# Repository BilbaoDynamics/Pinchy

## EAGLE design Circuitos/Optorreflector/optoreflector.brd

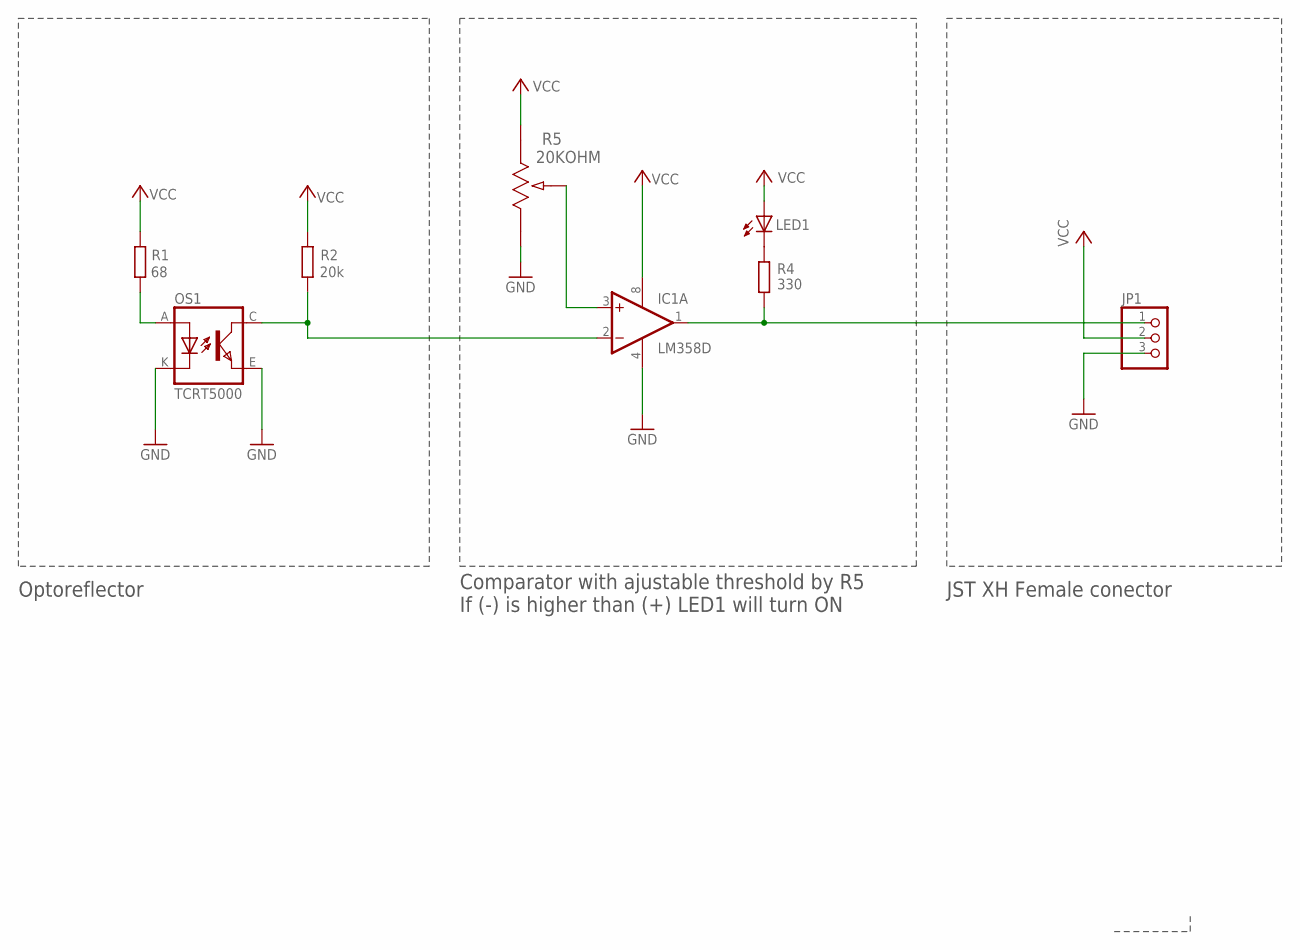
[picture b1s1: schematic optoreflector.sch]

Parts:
IC1: LM358D; SO08
JP1: PINHD-1X3; 1X03
LED1: LEDCHIP-LED0805; CHIP-LED0805
OS1: TCRT5000
R1: 68; R0805
R2: 20k; R0805
R4: 330; R0805
R5: 20KOHM; POT_EVM2W

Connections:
GND: IC1.4 (V-), JP1.3, OS1.E (EMITTER), OS1.K (CATHODE), R5.3
unnamed: LED1.C, R4.2
unnamed: OS1.A (ANODE), R1.1
unnamed: IC1.2 (-IN), OS1.C (COLLECTOR), R2.1
unnamed: IC1.3 (+IN), R5.2
unnamed: IC1.1 (OUT), JP1.1, R4.1
VCC: IC1.8 (V+), JP1.2, LED1.A, R1.2, R2.2, R5.1

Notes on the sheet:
Optoreflector
JST XH Female conector
Comparator with ajustable threshold by R5 If (-) is higher than (+) LED1 will turn ON

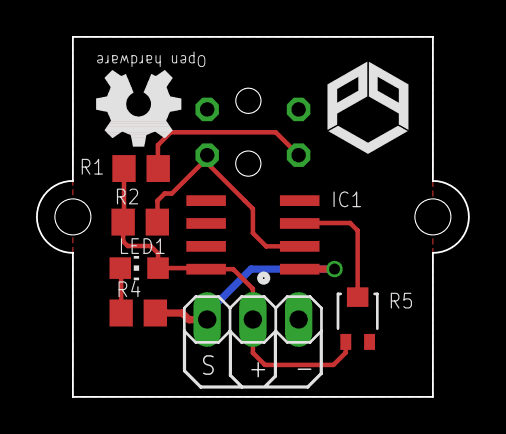
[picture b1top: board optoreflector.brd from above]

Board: 2 copper layers, 24.0 x 20.0 mm, 8 parts (1 on the bottom side), 7 nets.

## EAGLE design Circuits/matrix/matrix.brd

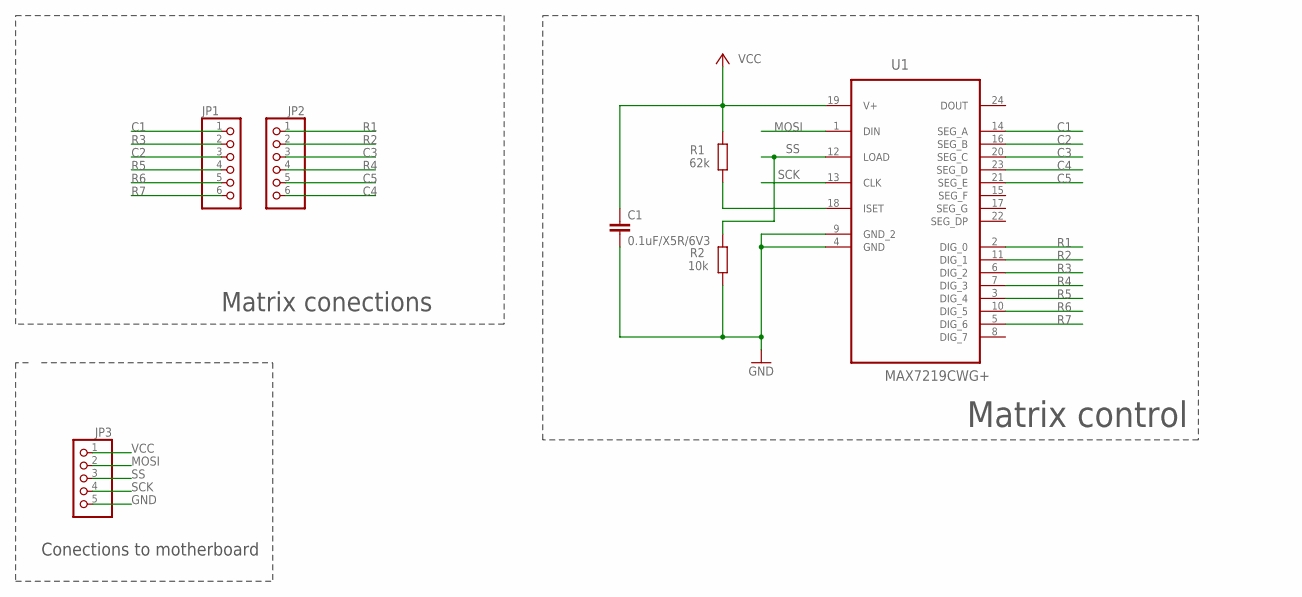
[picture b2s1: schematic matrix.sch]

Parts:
C1: 0.1uF/X5R/6V3; C1206
JP1, JP2: PINHD-1X6; 1X06
JP3: PINHD-1X5; 1X05
R1: 62k; R0805
R2: 10k; R0805
U1: MAX7219CWG+; SOIC127P1032X265-24N

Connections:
C1: JP1.1, U1.14 (SEG_A)
C2: JP1.3, U1.16 (SEG_B)
C3: JP2.3, U1.20 (SEG_C)
C4: JP2.6, U1.23 (SEG_D)
C5: JP2.5, U1.21 (SEG_E)
GND: C1.2, JP3.5, R2.1, U1.4 (GND), U1.9 (GND_2)
MOSI: JP3.2, U1.1 (DIN)
unnamed: R1.1, U1.18 (ISET)
R1: JP2.1, U1.2 (DIG_0)
R2: JP2.2, U1.11 (DIG_1)
R3: JP1.2, U1.6 (DIG_2)
R4: JP2.4, U1.7 (DIG_3)
R5: JP1.4, U1.3 (DIG_4)
R6: JP1.5, U1.10 (DIG_5)
R7: JP1.6, U1.5 (DIG_6)
SCK: JP3.4, U1.13 (CLK)
SS: JP3.3, R2.2, U1.12 (LOAD)
VCC: C1.1, JP3.1, R1.2, U1.19 (V+)

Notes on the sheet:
Matrix conections
Conections to motherboard
Matrix control

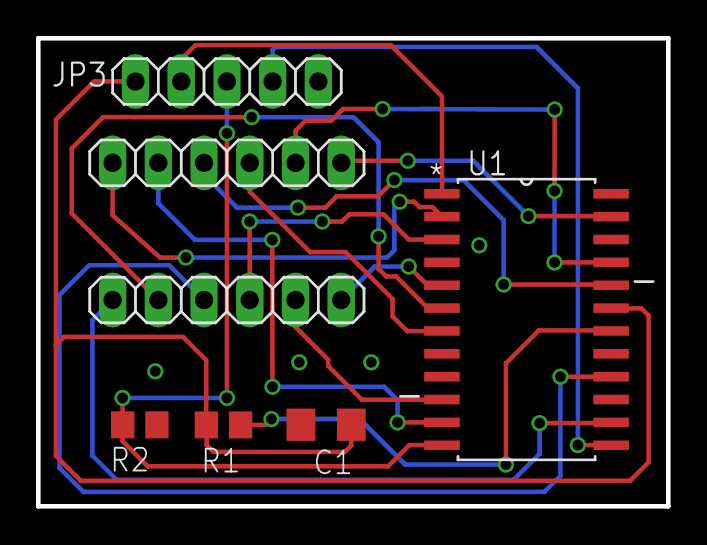
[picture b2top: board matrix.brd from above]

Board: 2 copper layers, 35.0 x 26.0 mm, 7 parts (0 on the bottom side), 18 nets.

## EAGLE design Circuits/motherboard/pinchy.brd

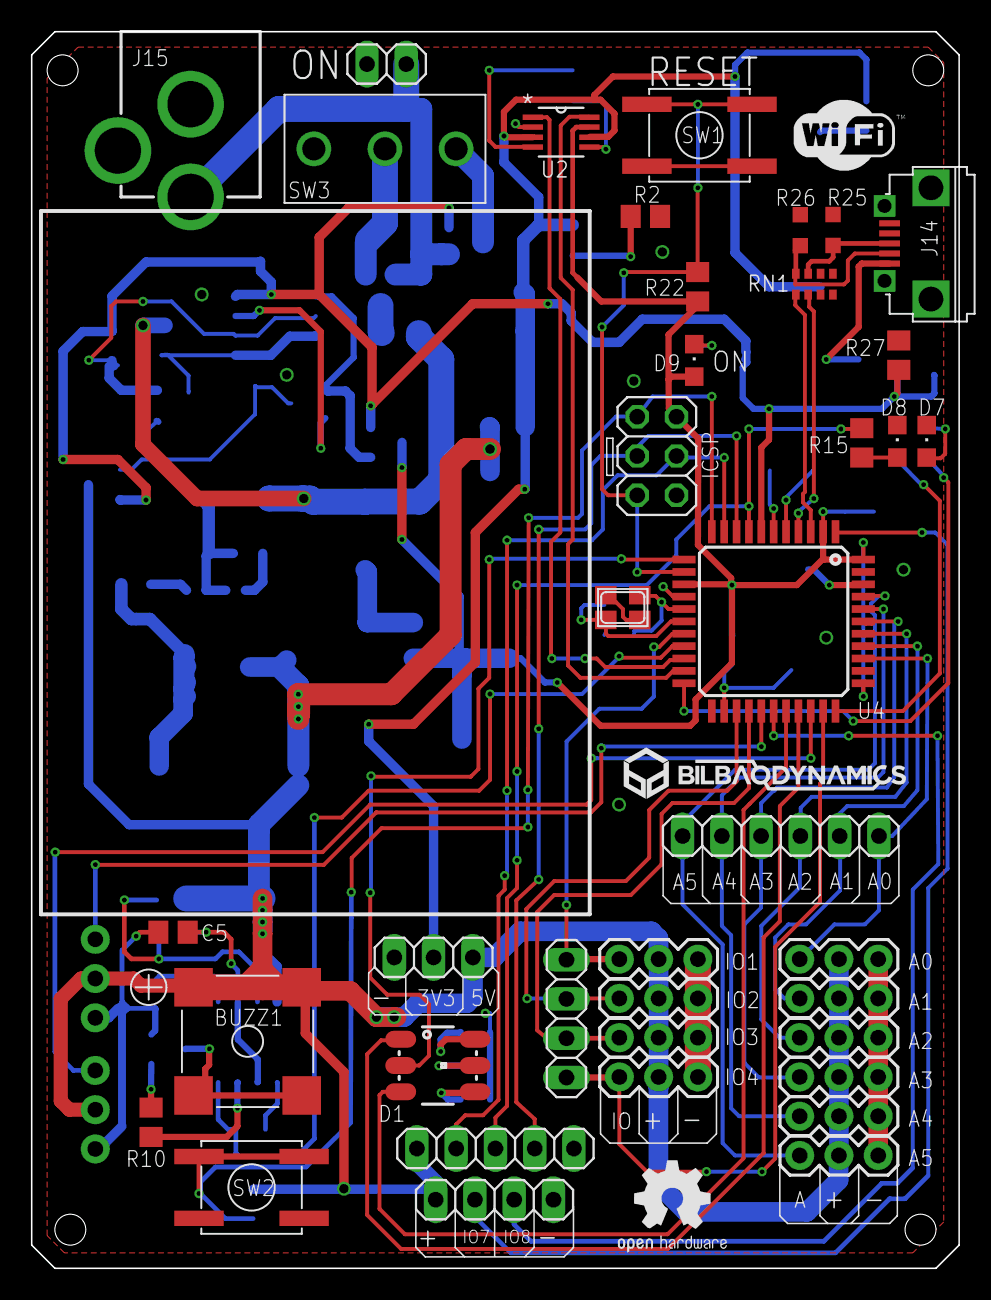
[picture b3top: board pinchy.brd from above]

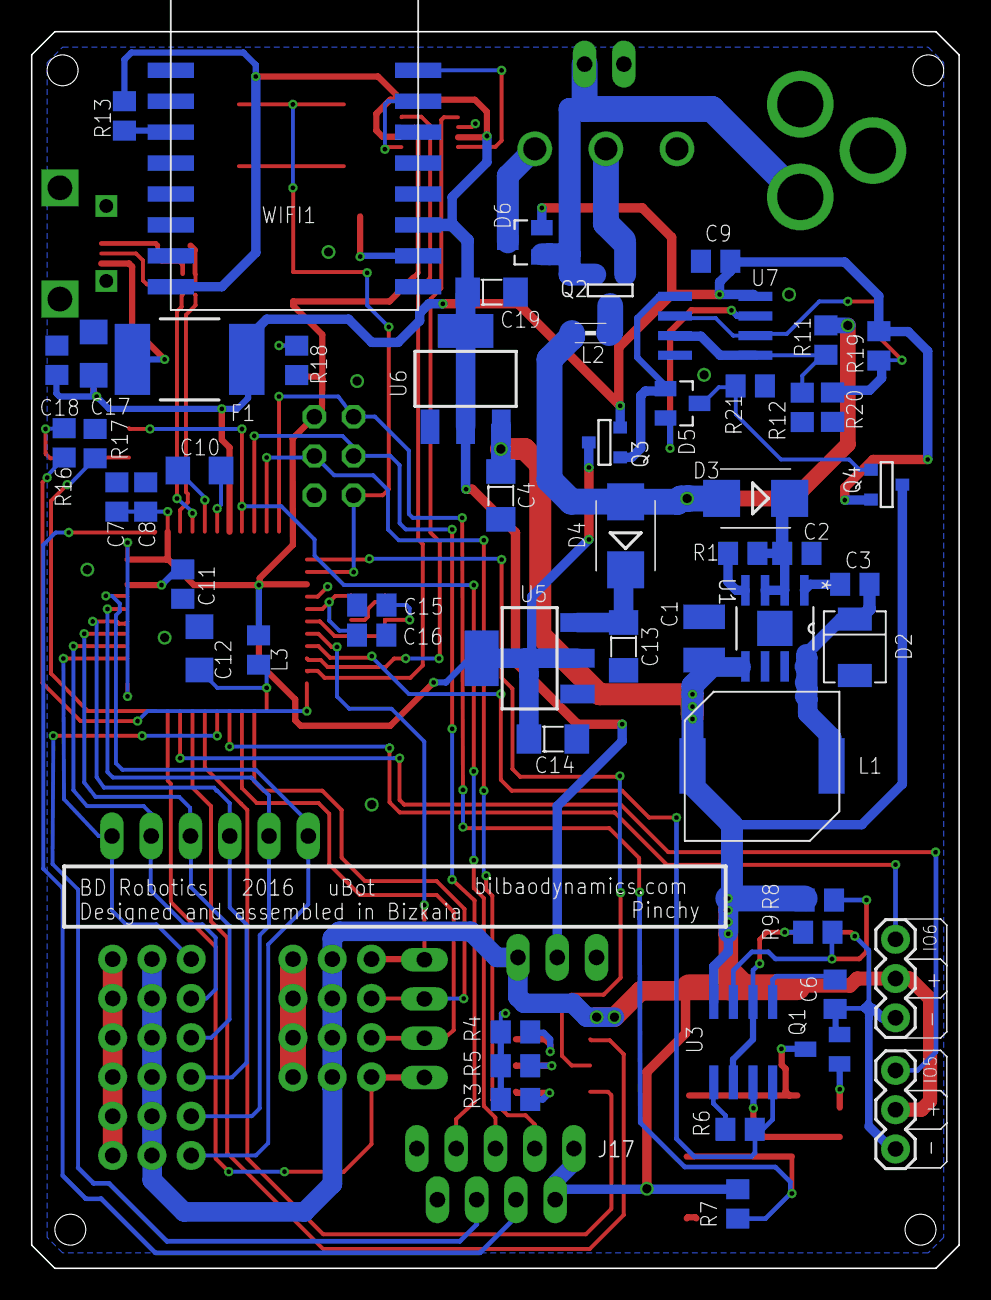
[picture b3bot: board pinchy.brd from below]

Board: 2 copper layers, 60.0 x 80.0 mm, 95 parts (56 on the bottom side), 73 nets.

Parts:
BUZZ1: KSSG74B16
C1: 47uF/X5R/6.3V; C1210
C2: 10uF/X5R/25V; C0805
C3, C6, C7, C8, C9, C11, C18: 0.1uF/X5R/6V3; C0805
C4, C13: 10uF/Tan/25V; C1206-POL
C5: 220nF/X5R/6V3; C0805
C10, C12: 1uF/X5R/16V; C1206
C14, C19: 22uF/tan/6V3; C1206-POL
C15, C16: 12pF/NP0; C0805
C17: 0.1uF/X5R/6V3; C1206
D1: LED-TRICOLOR-5050NO_IC; LED-TRICOLOR-5050
D2: SSB43L
D3, D4: PMEG3030EP; SMB
D5, D6: BAT54C; SOT23
D7: Yellow TX LED; CHIPLED_0805
D8: Yellow RX LED; CHIPLED_0805
D9: GREEN PWR_ON; CHIPLED_0805
F1: MF-MSMF050-2; SMD050F
J1: Tenacita; 1X03
J2: OptoreflectorA; 1X03
J3: ServoA; 1X03
J4: ServoB; 1X03
J5: OptoreflectorB; 1X03
J6: D13; 1X03
J7: AN0; 1X03
J8: AN1; 1X03
J9: AN2; 1X03
J10: AN3; 1X03
J11: AN4; 1X03
J12: AN5; 1X03
J13: I/O; 1X04
J14: ZX62D-B-5PA8(30)
J15: POWER_JACKPTH; POWER_JACK_PTH
J16: ICSP; 2X03
J17: Matrix; 1X05
J18: JST RCY; 1X02
J19: Utrasonic; 1X04
J20: Analogicas; 1X06
J21: Alimentacion; 1X03
L1: 4.7uH; TDK_VLF10040T_4R7N5R4
L2: EMI 742792012; 0805
L3: MH2029-300Y; R0805
Q1: BC847; SOT23
Q2: DMP3098L; SOT-23
Q3, Q4: DMP2035U-7; SOT-23
R1: 100k; R0805
R2, R13: 4K7; R0805
R3, R4, R5: 330; R0805
R6, R7, R17, R22, R27: 10k; R0805
R8: 820; R0805
R9: 750; R0805
R10, R15, R16, R18: 1k; R0805
R11, R19: 82k; R0805
R12, R20: 18k; R0805
R21: 51k; R0805
R25, R26: VARISTORCN0603; CT/CN0603
RN1: 22R; CAY16
SW1, SW2: EVQQ2; JAEGGER_MKII_EVQQ2
SW3: MFP106D
U1: ADP2303ARDZ-5.0; SOIC127P600X175-9N
U2: TCA9406DCTR; SOP65P400X130-8N
U3: LM555D; SO08
U4: ATMEGA32U4-AU; TQFP44
U5: LM1117MPX-5.0; SOT223
U6: LM1117MPX-3.3; SOT223
U7: LMV358; SO08
WIFI1: ESP8622-12E
XTAL: 16MHz; NX3225

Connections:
+3.3V: C19.2, J21.2, R13.2, U2.3, U2.6, U6.2, U6.TAB, WIFI1.GPIO2, WIFI1.VCC
+5V: BUZZ1.P$2, BUZZ1.P$3, C1.1, C4.2, J1.2, J2.2, J3.2, J4.2, J5.2, J6.2, J7.2, J8.2, J9.2, J10.2, J11.2, J12.2, J17.1, J19.1, J21.1, L1.2, Q4.1, R7.2, R8.2, U1.5, U3.8, U6.3
+5V_REG: C7.1, C8.1, C14.2, D9.A, J16.2, L3.1, Q3.1, R22.2, U2.7, U4.2, U4.14, U4.34, U4.44, U5.2, U5.TAB
A0: J7.1, J20.6, U4.36
A1: J8.1, J20.5, U4.37
A2: J9.1, J20.4, U4.38
A3: J10.1, J20.3, U4.39
A4: J11.1, J20.2, U4.40
A5: J12.1, J20.1, U4.41
D0/RX: U2.1, U4.20
D1/TX: U2.8, U4.21
D2: R6.1, U3.4, U4.19
D3: J1.1, J13.1, U4.18
D4: J2.1, J13.2, U4.25
D5: J3.1, U4.31
D6: J4.1, U4.27
D7: J19.2, U4.1
D8: J19.3, U4.28
D9: D1.3, U4.29
D10: D1.1, U4.30
D11: D1.2, U4.12
D12: J5.1, J13.3, U4.26
D13: J6.1, J13.4, U4.32
D14/MISO: J16.1, R7.1, SW2.P$1, SW2.P$4, U4.11
D15/SCK: J16.3, J17.4, U4.9
D16/MOSI: J16.4, J17.2, U4.10
D17/SS: J17.3, R15.1, U4.8
GND: C1.2, C2.2, C4.1, C5.2, C6.2, C7.2, C8.2, C9.2, C10.2, C11.2, C12.2, C13.1, C14.1, C15.2, C16.2, C17.2, C18.2, C19.1, D2.2, D7.C, D8.C, J1.3, J2.3, J3.3, J4.3, J5.3, J6.3, J7.3, J8.3, J9.3, J10.3, J11.3, J12.3, J14.GND, J14.P$1, J14.P$2, J14.P$6, J14.P$7, J15.GND, J15.GNDBREAK, J16.6, J17.5, J18.2, J19.4, J21.3, Q1.2, R2.2, R3.1, R4.1, R5.1, R6.2, R12.1, R17.2, R18.1, R20.1, R21.1, R25.1, R26.1, R27.1, SW1.P$2, SW1.P$3, SW2.P$2, SW2.P$3, SW3.2, U1.7, U2.2, U3.1, U4.5, U4.15, U4.23, U4.35, U4.43, U5.1, U6.1, U7.4, WIFI1.GND, XTAL.2, XTAL.4
HWB: R17.1, U4.33
unnamed: R8.1, R9.2, U3.7
unnamed: R10.2, U3.3
unnamed: D1.4, R3.2
unnamed: D1.6, R4.2
unnamed: C2.1, D3.C, R1.2, U1.2, U1.3
unnamed: D1.5, R5.2
unnamed: R13.1, WIFI1.EN
unnamed: R1.1, U1.4
unnamed: BUZZ1.P$1, BUZZ1.P$4, Q1.3
unnamed: C5.1, R9.1, U3.2, U3.6
unnamed: C3.2, D2.1, L1.1, U1.8
unnamed: C6.1, U3.5
unnamed: Q1.1, R10.1
unnamed: R2.1, WIFI1.GPIO15
unnamed: J14.D+, R25.2, RN1.7
unnamed: J14.D-, R26.2, RN1.8
unnamed: D6.1, J15.PWR, J18.1, Q2.2
unnamed: D5.3, Q4.3, R21.2
unnamed: F1.1, J14.VUSB
unnamed: L2.1, Q2.1
unnamed: R11.1, R12.2, U7.3, U7.5
unnamed: C3.1, U1.1
unnamed: D5.1, Q3.3, U7.1
unnamed: C15.1, U4.17, XTAL.1
unnamed: C16.1, U4.16, XTAL.3
unnamed: C10.1, U4.6
unnamed: C12.1, L3.2, U4.24
unnamed: D8.A, R15.2
unnamed: Q2.3, SW3.COM
unnamed: D6.3, SW3.1
unnamed: C13.2, D4.C, U5.3
unnamed: D9.C, R18.2
unnamed: D7.A, R16.2
unnamed: D5.2, U7.7
unnamed: R19.1, R20.2, U7.2, U7.6
RD_N: RN1.1, U4.3
RD_P: RN1.2, U4.4
RESET: J16.5, R22.1, SW1.P$1, SW1.P$4, U4.13
RXD_3.3: U2.5, WIFI1.RXD
TXD_3.3: U2.4, WIFI1.TXD
TX_LED: R16.1, U4.22
U4: C11.1, U4.42
VCC: D3.A, D4.A, L2.2, R11.2
VUSB: C9.1, C17.1, C18.1, D6.2, F1.2, Q3.2, Q4.2, R19.2, R27.2, U4.7, U7.8

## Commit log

2016-11-18 ❌ Deleted unused files
2016-11-18 🚀 Updated for the newest version of Pinchy
2016-11-20 Sistema WEB -(internet)-> OpenServer -(Internet)-> NattedServer -(wifi/serial)-> Arduino
2017-03-03 Añadido README y cambiados nombres
2017-03-03 Añadido README
2017-03-03 Minor changes
2017-03-03 Added script to burn ATMega324 to Pinchy

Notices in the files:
parts and their libraries:
SparkFun-LED: Licensing: Creative Commons ShareAlike 4.0 International - https://creativecommons.org/licenses/by-sa/4.0
